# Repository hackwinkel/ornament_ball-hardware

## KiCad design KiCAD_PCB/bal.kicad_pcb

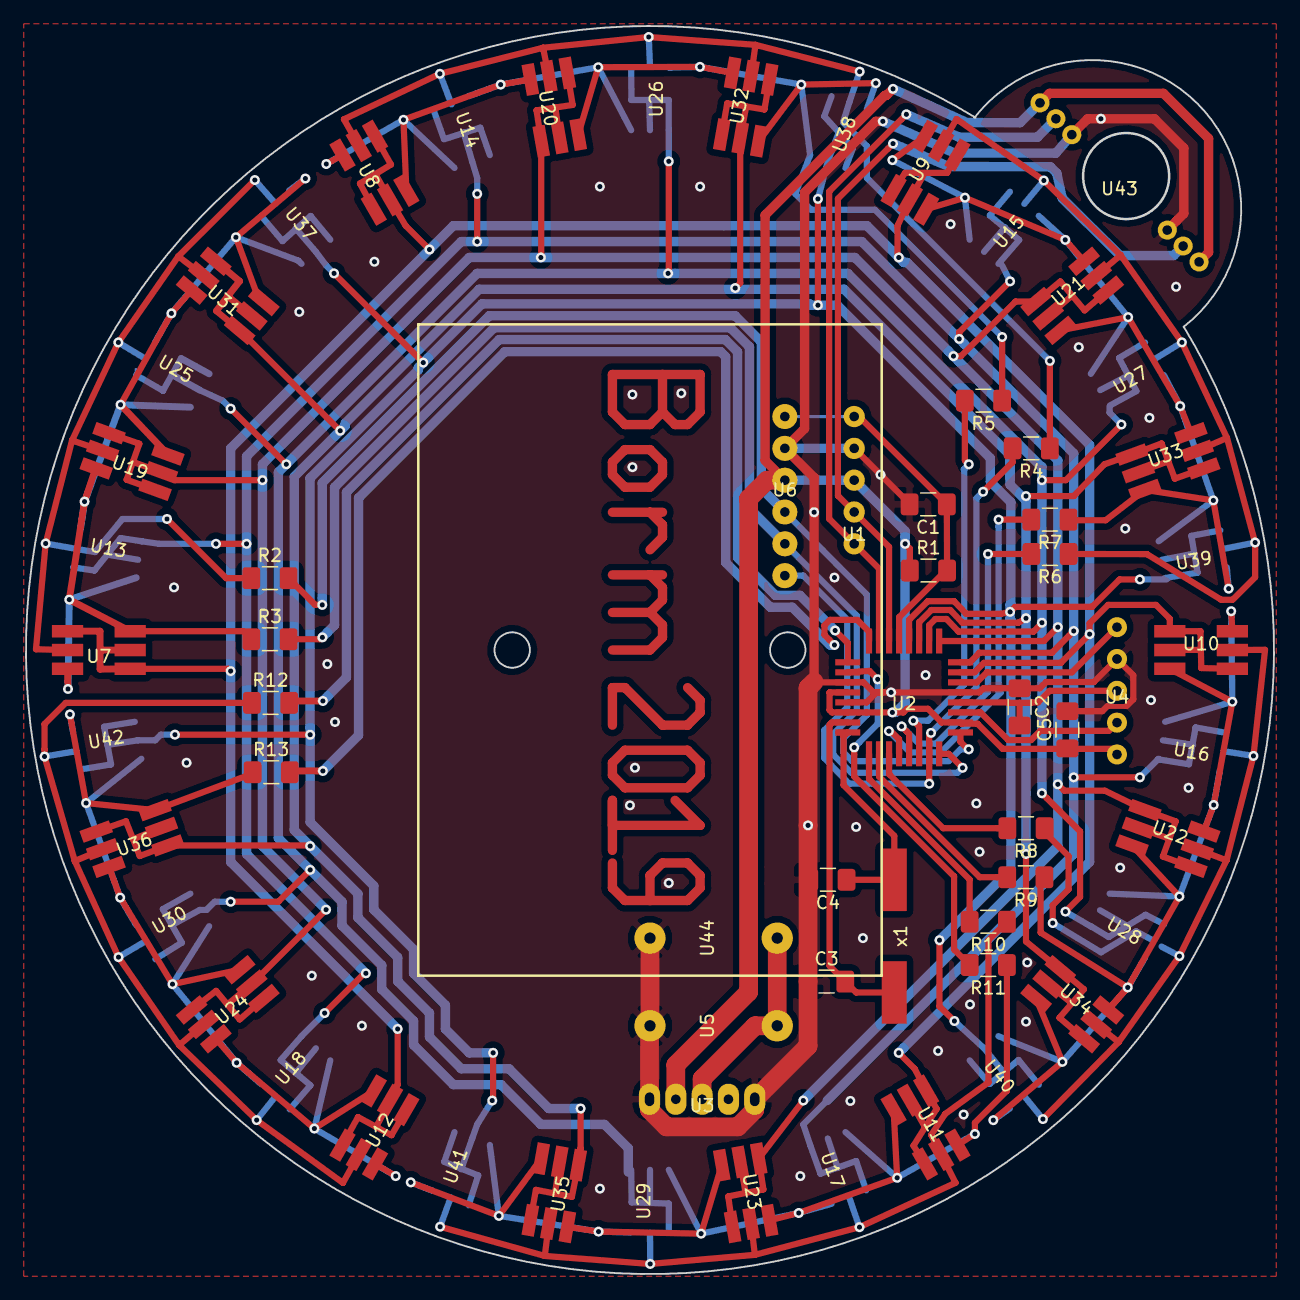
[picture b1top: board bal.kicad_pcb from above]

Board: 2 copper layers, 99.6 x 99.6 mm, 63 parts (0 on the bottom side), 41 nets.

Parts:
C1, C2, C5: 100nF; C_1206_3216Metric_Pad1.42x1.75mm_HandSolder
C3, C4: 22pf; C_1206_3216Metric_Pad1.42x1.75mm_HandSolder
R1: 33k; R_1206_3216Metric_Pad1.42x1.75mm_HandSolder
R2, R4, R6, R8, R10, R12: 100; R_1206_3216Metric_Pad1.42x1.75mm_HandSolder
R3, R5, R7, R9, R11, R13: 56; R_1206_3216Metric_Pad1.42x1.75mm_HandSolder
U1: sercon
U2: atm328
U3: switch
U4: aconn
U5, U44: powcon; powconn
U6: procon
U7, U8, U9, U10, U11, U12, U19, U20, U21, U22, U23, U24, U31, U32, U33, U34, U35, U36: rgbled
U13, U14, U15, U16, U17, U18, U25, U26, U27, U28, U29, U30, U37, U38, U39, U40, U41, U42: rgbled; rgbled2
U43: scon2
x1: xtal

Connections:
+5V: C5.1, R1.1, U1.1, U2.4, U2.6, U2.18, U3.2, U4.5, U6.1, U43.1, U43.6
GND: C1.2, C2.1, C3.1, C4.2, C5.2, U1.4, U2.3, U2.5, U2.21, U3.1, U3.5, U4.2, U5.2, U6.2, U43.3, U43.4, U44.2
unnamed: C1.1, R1.2, U1.5, U2.29, U6.3
unnamed: C2.2, U2.20, U4.3
unnamed: C3.2, U2.7, x1.1
unnamed: C4.1, U2.8, x1.2
unnamed: R2.1, U7.2, U13.2, U19.2, U25.2, U31.2, U37.2
unnamed: R2.2, U2.17, U6.6
unnamed: R3.1, U7.3, U7.6, U13.3, U13.6, U19.3, U19.6, U25.3, U25.6, U31.3, U31.6, U37.3, U37.6
unnamed: R3.2, U2.16, U6.5
unnamed: R4.1, U8.2, U14.2, U20.2, U26.2, U32.2, U38.2
unnamed: R4.2, U2.15, U6.4
unnamed: R5.1, U8.3, U8.6, U14.3, U14.6, U20.3, U20.6, U26.3, U26.6, U32.3, U32.6, U38.3, U38.6
unnamed: R5.2, U2.14
unnamed: R6.1, U9.2, U15.2, U21.2, U27.2, U33.2, U39.2
unnamed: R6.2, U2.13
unnamed: R7.1, U9.3, U9.6, U15.3, U15.6, U21.3, U21.6, U27.3, U27.6, U33.3, U33.6, U39.3, U39.6
unnamed: R7.2, U2.12
unnamed: R8.1, U10.2, U16.2, U22.2, U28.2, U34.2, U40.2
unnamed: R8.2, U2.11
unnamed: R9.1, U10.3, U10.6, U16.3, U16.6, U22.3, U22.6, U28.3, U28.6, U34.3, U34.6, U40.3, U40.6
unnamed: R9.2, U2.10
unnamed: R10.1, U11.2, U17.2, U23.2, U29.2, U35.2, U41.2
unnamed: R10.2, U2.9
unnamed: R11.1, U11.3, U11.6, U17.3, U17.6, U23.3, U23.6, U29.3, U29.6, U35.3, U35.6, U41.3, U41.6
unnamed: R11.2, U2.2
unnamed: R12.1, U12.2, U18.2, U24.2, U30.2, U36.2, U42.2
unnamed: R12.2, U2.1
unnamed: R13.1, U12.3, U12.6, U18.3, U18.6, U24.3, U24.6, U30.3, U30.6, U36.3, U36.6, U42.3, U42.6
unnamed: R13.2, U2.32
unnamed: U1.2, U2.30, U43.2
unnamed: U1.3, U2.31, U43.5
unnamed: U2.19, U4.4
unnamed: U2.22, U4.1
unnamed: U2.26, U25.1, U25.4, U25.5, U26.1, U26.4, U26.5, U27.1, U27.4, U27.5, U28.1, U28.4, U28.5, U29.1, U29.4, U29.5, U30.1, U30.4, U30.5
unnamed: U2.27, U31.1, U31.4, U31.5, U32.1, U32.4, U32.5, U33.1, U33.4, U33.5, U34.1, U34.4, U34.5, U35.1, U35.4, U35.5, U36.1, U36.4, U36.5
unnamed: U2.28, U37.1, U37.4, U37.5, U38.1, U38.4, U38.5, U39.1, U39.4, U39.5, U40.1, U40.4, U40.5, U41.1, U41.4, U41.5, U42.1, U42.4, U42.5
unnamed: U3.3, U5.1, U44.1
unnamed: U2.23, U7.1, U7.4, U7.5, U8.1, U8.4, U8.5, U9.1, U9.4, U9.5, U10.1, U10.4, U10.5, U11.1, U11.4, U11.5, U12.1, U12.4, U12.5
unnamed: U2.24, U13.1, U13.4, U13.5, U14.1, U14.4, U14.5, U15.1, U15.4, U15.5, U16.1, U16.4, U16.5, U17.1, U17.4, U17.5, U18.1, U18.4, U18.5
unnamed: U2.25, U19.1, U19.4, U19.5, U20.1, U20.4, U20.5, U21.1, U21.4, U21.5, U22.1, U22.4, U22.5, U23.1, U23.4, U23.5, U24.1, U24.4, U24.5

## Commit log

2020-09-22 initial commit of a 36 RGB led charlie-multi-plexed ornament
2020-09-27 added PDF schematic
